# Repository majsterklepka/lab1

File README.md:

# Electronics Workshops
electronics laboratory

Hi! Here is my job, passion and profession. This repository is part of my electronic workbench. Here I will be publish my project used in my everyday jobs. I think it so ourselves, that is cheap as will be buy in the online shops, and I do that.

What will be included into repository:

- power supplies
- dev board
- voltmeters, ammeters, frequency meters, RLC meters etc.
- multiple different usage modules usually used in the laboratory
- etc. ...

## Credits

Author: SQ7EQE op Paweł

Personal blog: [majsterklepka.github.io](https://majsterklepka.github.io/ "My Personal Blog")

Contents of that repository are licensed under terms of:

- GNU GPLv3
- GNU FDL-1.3
- CC-BY-SA, in some reason

**Note:**  
> _Carefully read license, remember the Author, his work is worth something! If you don't want to praise, don't criticize. You can freely modify the projects contained in this repository, remember that!_

**© Paweł Sobótka, 2019 all rights reserved**

At the end ... have fun! Feel free & share these projects with friends!

_MSc Paweł Sobótka (SQ7EQE)_

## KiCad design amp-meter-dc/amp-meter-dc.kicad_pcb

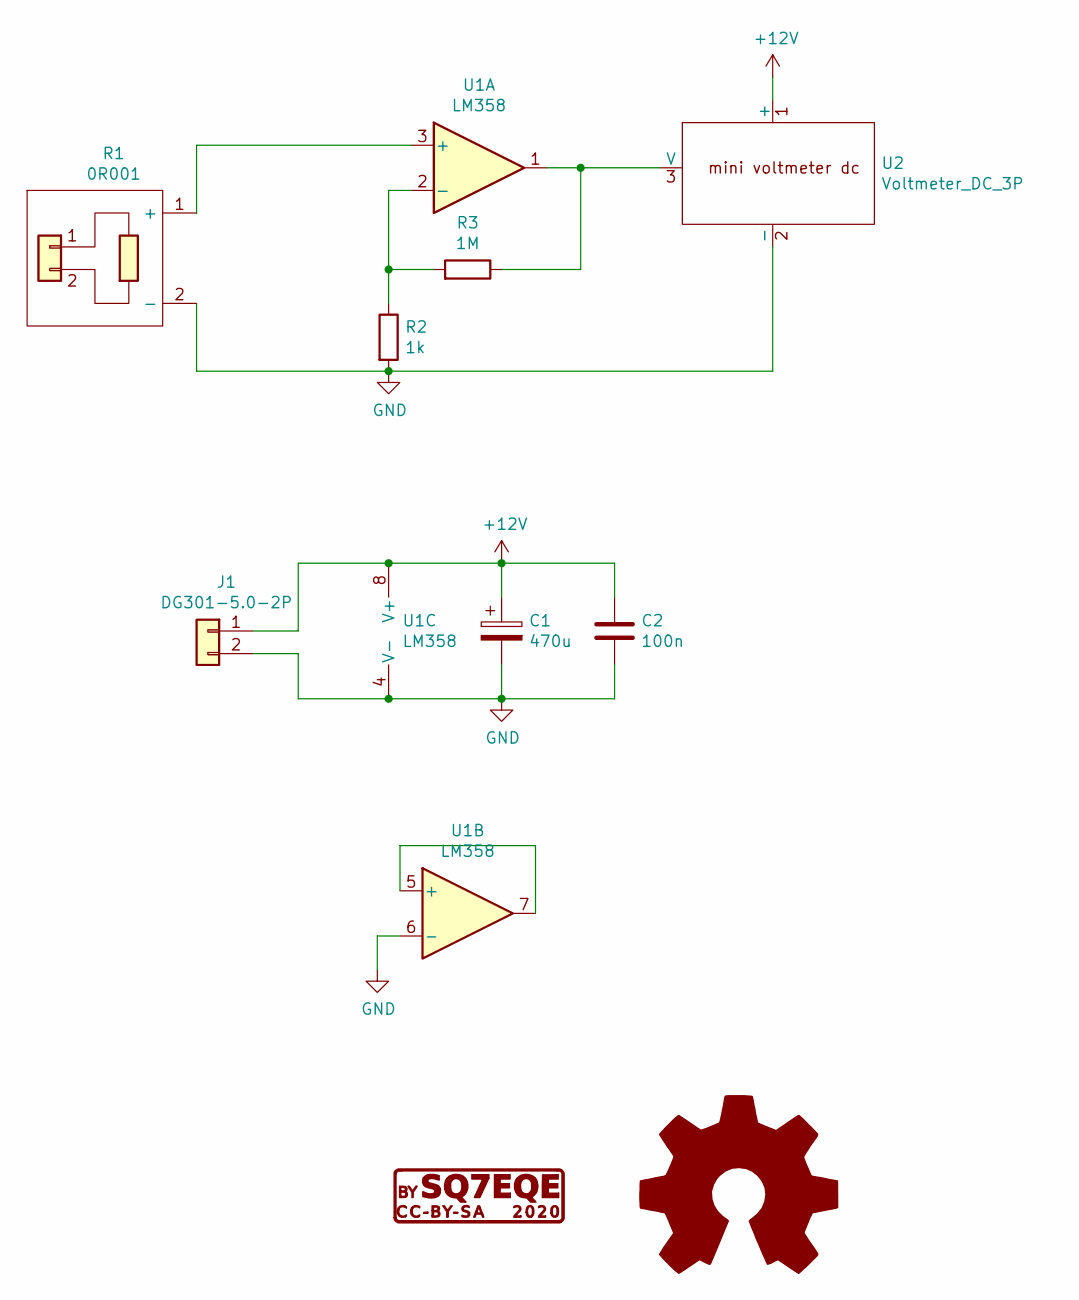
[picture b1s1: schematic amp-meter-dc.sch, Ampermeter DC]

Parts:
C1: 470u; CP_Radial_D8.0mm_P5.00mm
C2: 100n; C_Rect_L7.0mm_W2.0mm_P5.00mm
G1: CC-BY-SA; cc-by-sa
G2: Logo_Open_Hardware_Large; OSHW-Logo2_9.8x8mm_SilkScreen
J1: DG301-5.0-2P
R1: 0R001; bocznik-001
R2: 1k; R_Axial_DIN0204_L3.6mm_D1.6mm_P7.62mm_Horizontal
R3: 1M; R_Axial_DIN0204_L3.6mm_D1.6mm_P7.62mm_Horizontal
U1: LM358; DIP-8_W7.62mm
U2: Voltmeter_DC_3P; mini-voltmeter-dc

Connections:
+12V: C1.1, C2.1, J1.1, U1.8 (V+), U2.1 (+)
GND: C1.2, C2.2, J1.2, R1.2 (-), R2.2, U1.4 (V-), U1.6 (-), U2.2 (-)
unnamed: R1.1 (+), U1.3 (+)
unnamed: R2.1, R3.2, U1.2 (-)
unnamed: R3.1, U1.1, U2.3 (V)
unnamed: U1.5 (+), U1.7

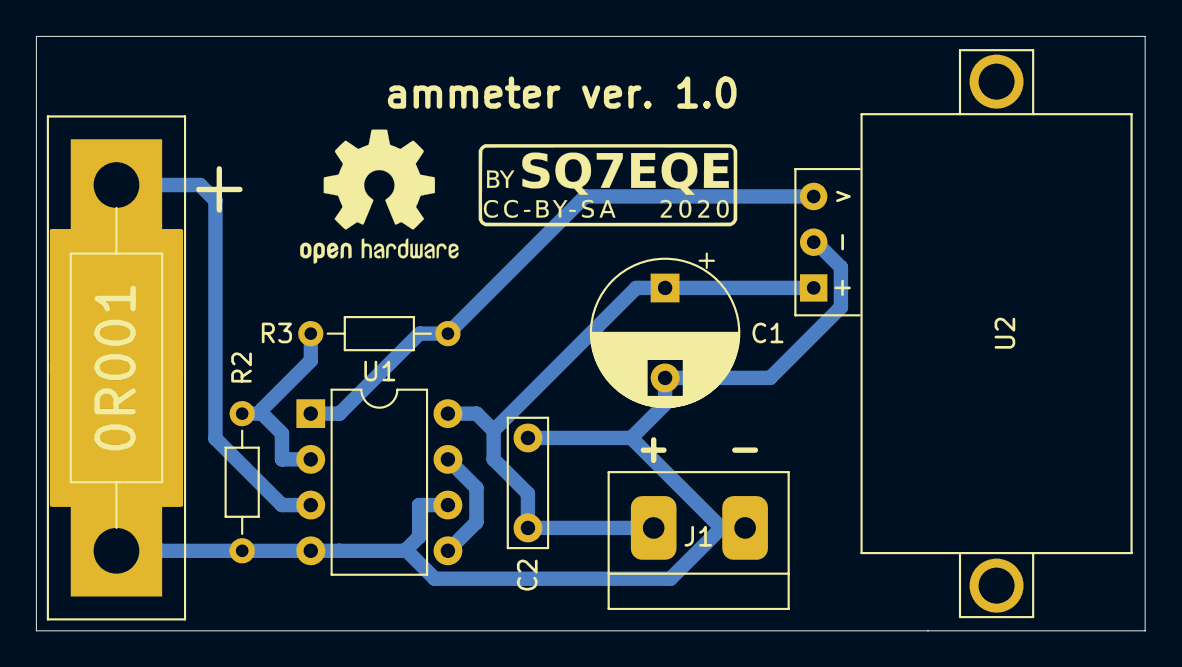
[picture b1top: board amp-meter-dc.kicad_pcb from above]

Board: 2 copper layers, 61.6 x 33.0 mm, 10 parts (0 on the bottom side), 6 nets.

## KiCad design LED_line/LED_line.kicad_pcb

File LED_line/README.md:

# LED strip with eight diodes
electronics workshop

Hi! LED strip for use in any project, inspired by the [avr-gcc](http://hobby.abxyz.bplaced.net/index.php?pid=4&cid=1 "Internetowy kurs avr-gcc") course. Below a PCB 3D view, next as description picture up.

Here we have a schematic sheet:

And what is obviously, project of PCB:

Of course, all project files are included in this folder, with Gerber picture too. Project is very easy to copy, doesn't needs dual side laminate, can be make with thermotransfer method of PCB production in home workshops laboratory.

Have a fun with that project! Be carefully of hot iron!

_MSc. Paweł Sobótka (SQ7EQE)_

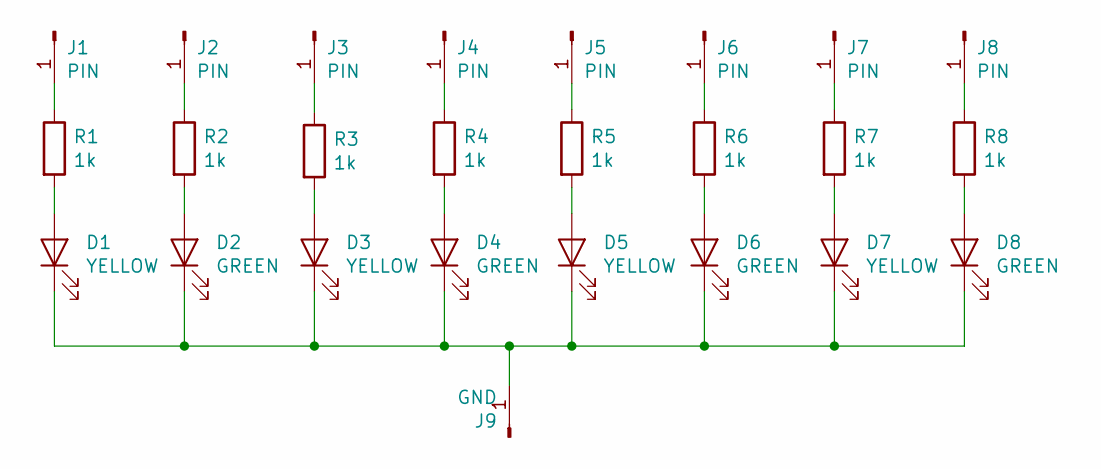
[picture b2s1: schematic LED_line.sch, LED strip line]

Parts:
D1, D3, D5, D7: YELLOW; LED_D3.0mm
D2, D4, D6, D8: GREEN; LED_D3.0mm
J1, J2, J3, J4, J5, J6, J7, J8: PIN; pin_in_01x01
J9: GND; pin_in_01x01
R1, R2, R3, R4, R5, R6, R7, R8: 1k; R_Axial_DIN0204_L3.6mm_D1.6mm_P7.62mm_Horizontal

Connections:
unnamed: D1.1 (K), D2.1 (K), D3.1 (K), D4.1 (K), D5.1 (K), D6.1 (K), D7.1 (K), D8.1 (K), J9.1
unnamed: D1.2 (A), R1.2
unnamed: D2.2 (A), R2.2
unnamed: D3.2 (A), R3.2
unnamed: D4.2 (A), R4.2
unnamed: D5.2 (A), R5.2
unnamed: D6.2 (A), R6.2
unnamed: D7.2 (A), R7.2
unnamed: D8.2 (A), R8.2
unnamed: J1.1, R1.1
unnamed: J2.1, R2.1
unnamed: J3.1, R3.1
unnamed: J4.1, R4.1
unnamed: J5.1, R5.1
unnamed: J6.1, R6.1
unnamed: J7.1, R7.1
unnamed: J8.1, R8.1

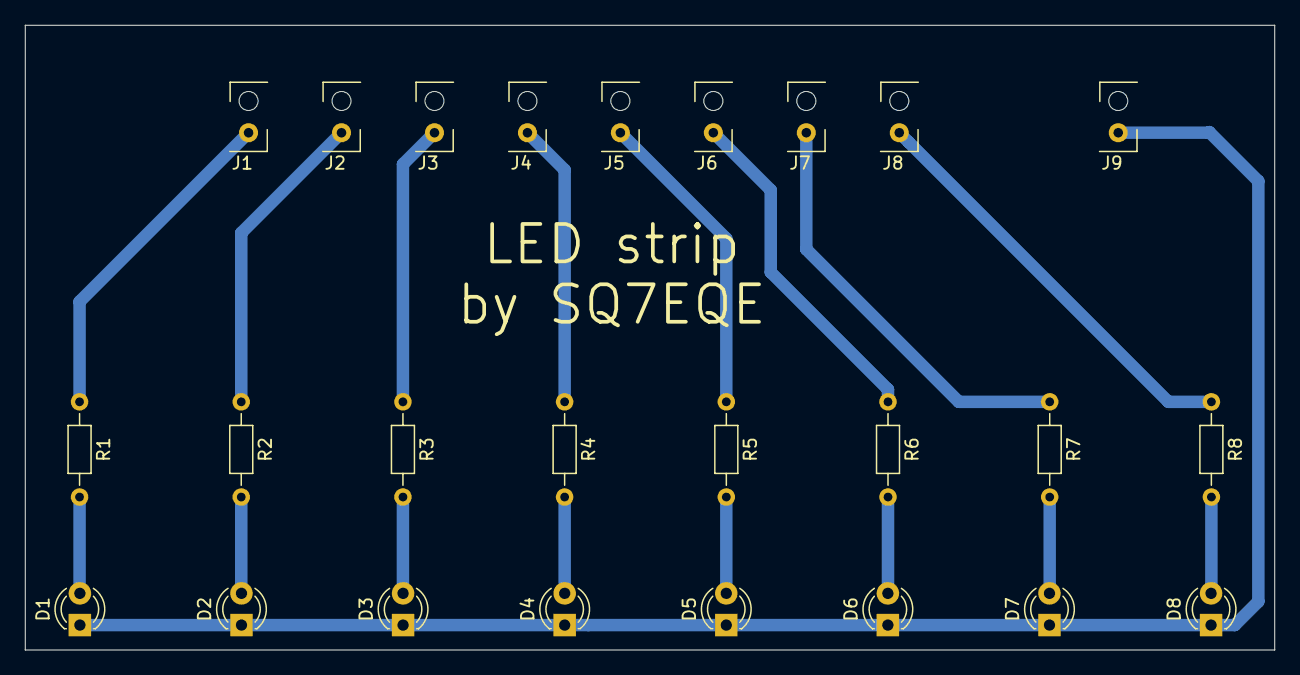
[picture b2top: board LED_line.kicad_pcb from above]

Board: 2 copper layers, 100.0 x 50.0 mm, 25 parts (0 on the bottom side), 17 nets.

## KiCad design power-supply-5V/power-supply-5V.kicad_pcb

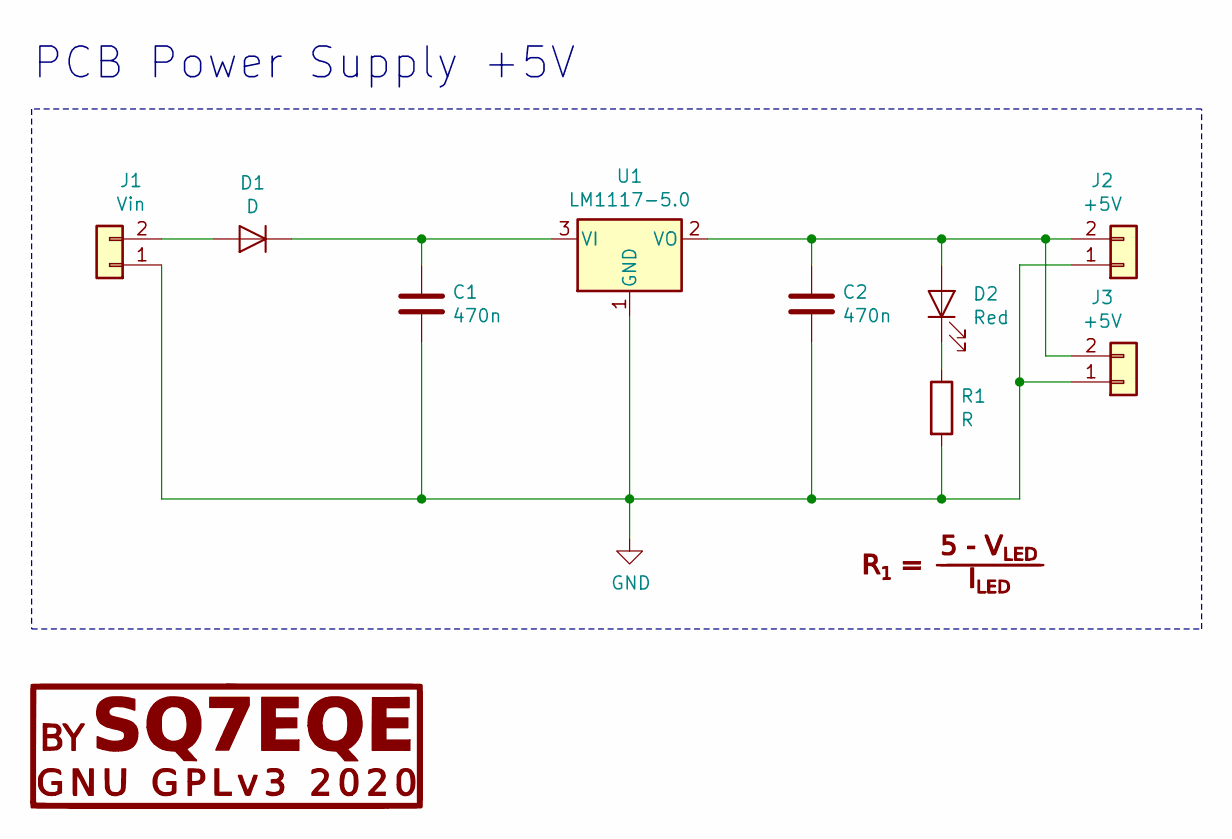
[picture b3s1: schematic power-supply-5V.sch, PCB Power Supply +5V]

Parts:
C1, C2: 470n; C_0805_2012Metric_Pad1.15x1.40mm_HandSolder
D1: D; D_1206_3216Metric_Pad1.42x1.75mm_HandSolder
D2: Red; LED_1206_3216Metric_Pad1.42x1.75mm_HandSolder
J1: Vin; conn_v_in_2x01_508
J2, J3: +5V; conn_v_out_2x03_2.54
R1: R; R_1206_3216Metric_Pad1.42x1.75mm_HandSolder
U1: LM1117-5.0; SOT-223

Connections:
GND: C1.2, C2.2, J1.1, J2.1, J3.1, R1.2, U1.1 (GND)
unnamed: C1.1, D1.1 (K), U1.3 (VI)
unnamed: C2.1, D2.2 (A), J2.2, J3.2, U1.2 (VO)
unnamed: D1.2 (A), J1.2
unnamed: D2.1 (K), R1.1

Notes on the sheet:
PCB Power Supply +5V

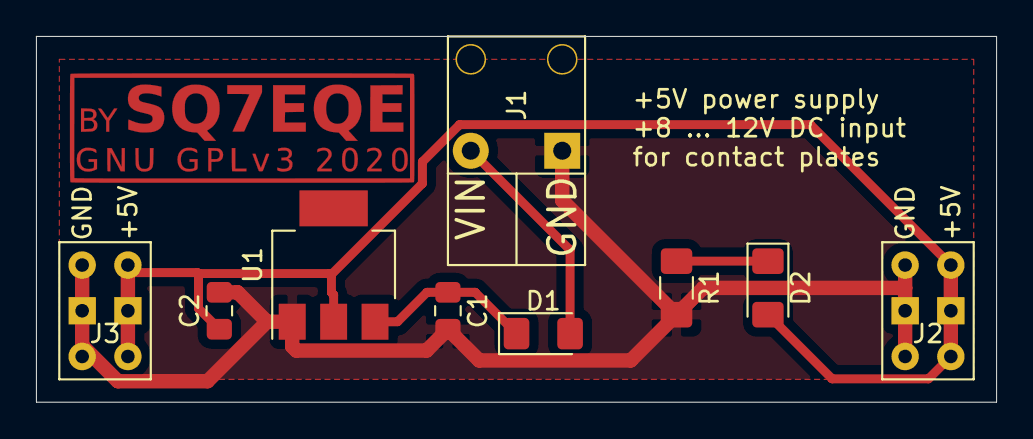
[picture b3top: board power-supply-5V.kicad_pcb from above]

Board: 2 copper layers, 53.3 x 20.3 mm, 9 parts (0 on the bottom side), 5 nets.

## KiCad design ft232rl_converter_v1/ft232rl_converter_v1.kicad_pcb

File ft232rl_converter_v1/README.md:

# USB-TTL-UART-FT232RL Converter
electronics laboratory

Hello, my dear friends!

Today I will tell you about the latest project, USB-TTL-UART-FT232RL converter. It can be said a flagship design, based on the catalog manufacturer's catalog notes. Below, 3D view of the circuit board.

The following elements are needed to build:

- printed circuit board, Gerber files are available in the folder plot /
- FT232RL, the device can be ordered online,
- 100nF x 2 capacitor,
- 10nF x 1 capacitor,
- 10k x 1 resistor,
- 12MHz quartz oscillator,
- ferrite bead x 1,
- MLCC capacitor, 10uF x 1,
- gold pins, straight and angled, 0.1 "pitch
- USB micro B x 1 socket,

The list of all required electronic components is included in the BOM file, available in CSV, ODS and HTML format available in the project's main directory. The schematic diagram of the system is presented below:

And here, an illustrative look at the layout of the circuit board:

It is a system using SMD elements and requires a certain skill in assembly from the contractor due to the size of the elements. All discrete, passive elements are in SMD1206 size and the FT232RL integrated circuit in SSOP-28.

Have fun, feel free and share this project with friends!

Project made available under the terms of the GNU GPLv3 license, project documentation made available under the terms of the FDL-1.3 license.

Thank you and welcome again!

_MSc. Paweł Sobótka (SQ7EQE)_

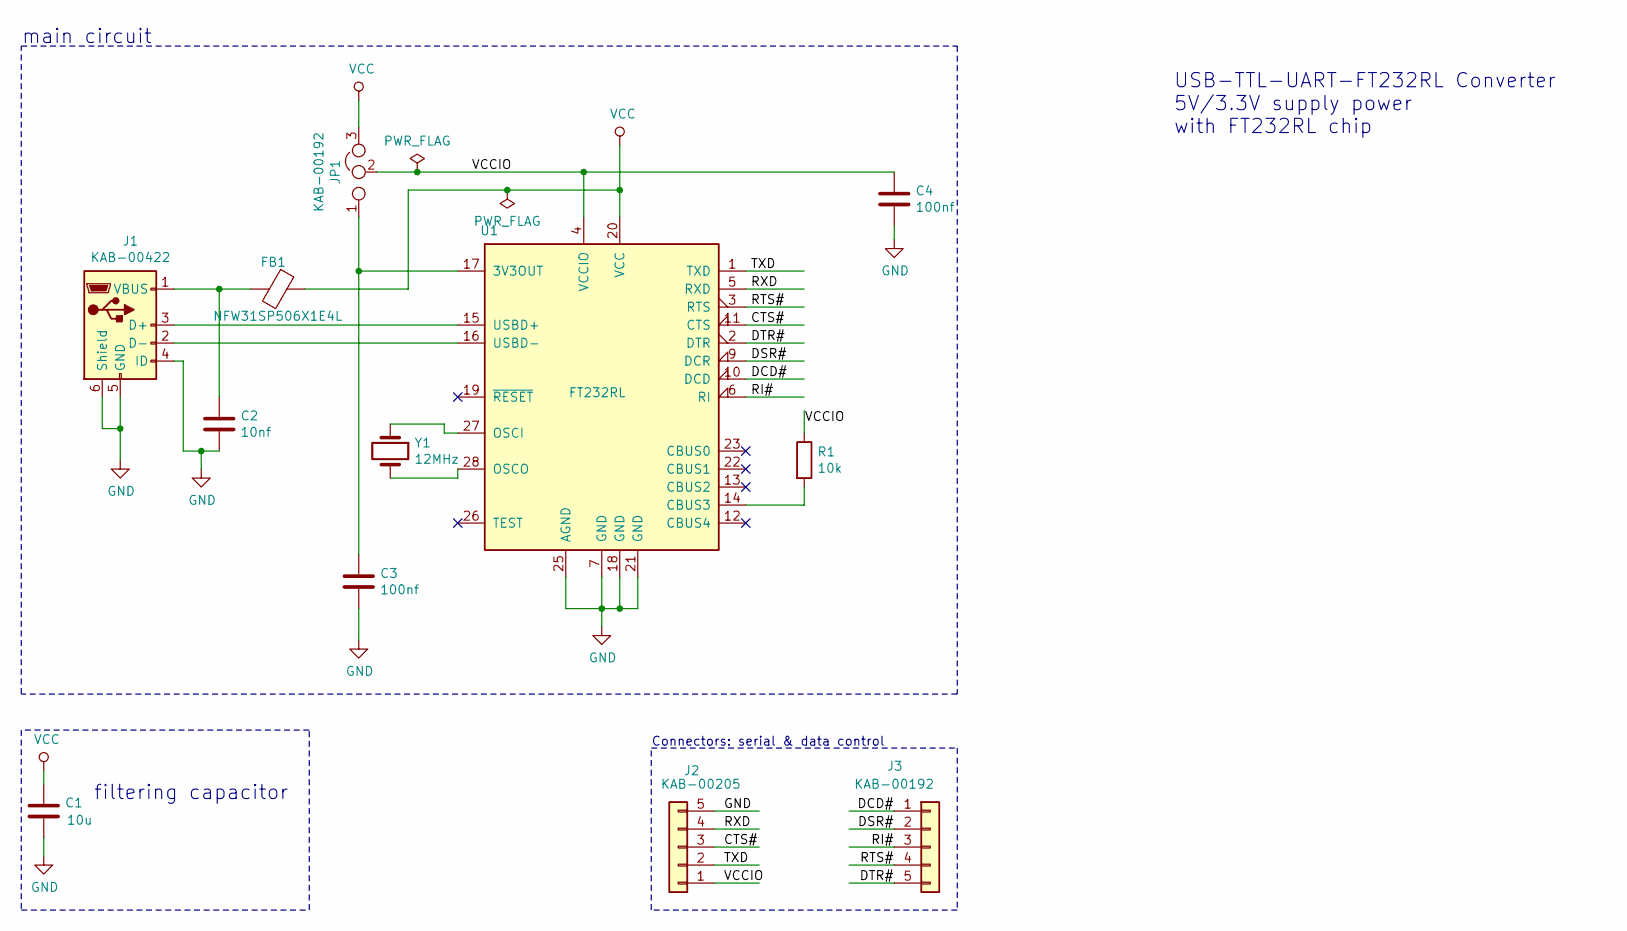
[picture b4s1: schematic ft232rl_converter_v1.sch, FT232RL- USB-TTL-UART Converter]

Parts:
C1: 10u; C_1206_3216Metric_Pad1.42x1.75mm_HandSolder; Part C1206C106K9RACTU
C2: 10nf; C_1206_3216Metric_Pad1.42x1.75mm_HandSolder; Part KC10nF_1206
C3, C4: 100nf; C_1206_3216Metric_Pad1.42x1.75mm_HandSolder; Part KC100nF_1206
FB1: NFW31SP506X1E4L; R_1206_3216Metric_Pad1.42x1.75mm_HandSolder; Part NFW31SP506X1E4L
J1: KAB-00422; USB_Micro-B_Molex_47346-0001; Part KAB-00422
J2: KAB-00205; PinHeader_1x05_P2.54mm_Horizontal; Part KAB-00205
J3: KAB-00192; PinHeader_1x05_P2.54mm_Vertical; Part KAB-00192
JP1: KAB-00192; PinHeader_1x03_P2.54mm_Vertical; Part KAB-00192
R1: 10k; R_1206_3216Metric_Pad1.42x1.75mm_HandSolder; Part R10K_1206
U1: FT232RL; SSOP-28_5.3x10.2mm_P0.65mm; Part FT232RL
Y1: 12MHz; Crystal_HC49-U_Vertical; Part Q12MHZ_N

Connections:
/CTS#: J2.3, U1.11 (CTS)
/DCD#: J3.1, U1.10 (DCD)
/DSR#: J3.2, U1.9 (DCR)
/DTR#: J3.5, U1.2 (DTR)
/RI#: J3.3, U1.6 (RI)
/RTS#: J3.4, U1.3 (RTS)
/RXD: J2.4, U1.5 (RXD)
/TXD: J2.2, U1.1 (TXD)
/VCCIO: C4.1, J2.1, JP1.2, R1.1, U1.4 (VCCIO)
GND: C1.2, C2.2, C3.2, C4.2, J1.4 (ID), J1.5 (GND), J1.6 (Shield), J2.5, U1.7 (GND), U1.18 (GND), U1.21 (GND), U1.25 (AGND)
unnamed: C2.1, FB1.2, J1.1 (VBUS)
unnamed: C3.1, JP1.1, U1.17 (3V3OUT)
unnamed: J1.2 (D-), U1.16 (USBD-)
unnamed: J1.3 (D+), U1.15 (USBD+)
unnamed: R1.2, U1.14 (CBUS3)
unnamed: U1.27 (OSCI), Y1.1
unnamed: U1.28 (OSCO), Y1.2
VCC: C1.1, FB1.1, JP1.3, U1.20 (VCC)

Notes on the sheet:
Connectors: serial & data control
filtering capacitor
USB-TTL-UART-FT232RL Converter 5V/3.3V supply power with FT232RL chip
main circuit

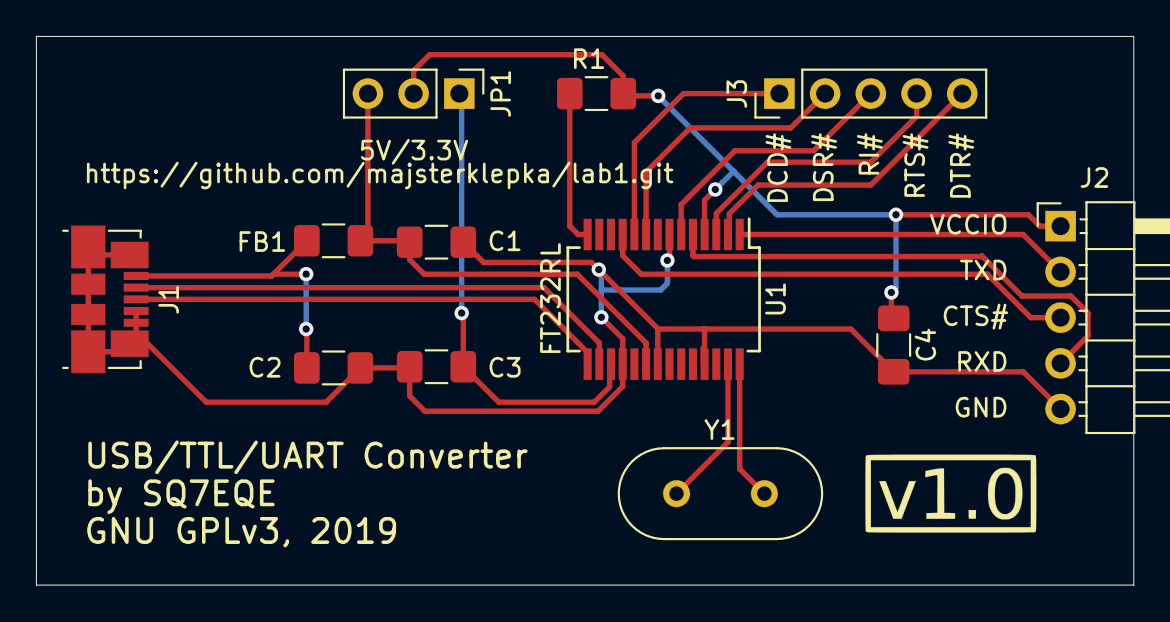
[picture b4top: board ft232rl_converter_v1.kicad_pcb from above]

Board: 2 copper layers, 61.0 x 30.5 mm, 12 parts (0 on the bottom side), 18 nets.

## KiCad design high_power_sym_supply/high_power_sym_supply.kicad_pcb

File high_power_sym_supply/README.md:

# AC/DC symmetric supply
electronics workshop

Hi, My Friends!

Today, I present you with an ac/dc symmetric supply. This project is simply to reproduce, you can use a standard Thermo transfer method, widely described at YouTube. Below you can see a 3D view of PCB layout with components:

Here you can see a schematics sheet, it is very easy, you can reproduce it as you wish:

Of course in that folder, I have included all project files, with Gerber files too.

And here you can see a 2D view of PCB layout:

Have fun & share that project with your friends!

_MSc. Paweł Sobótka (SQ7EQE)_

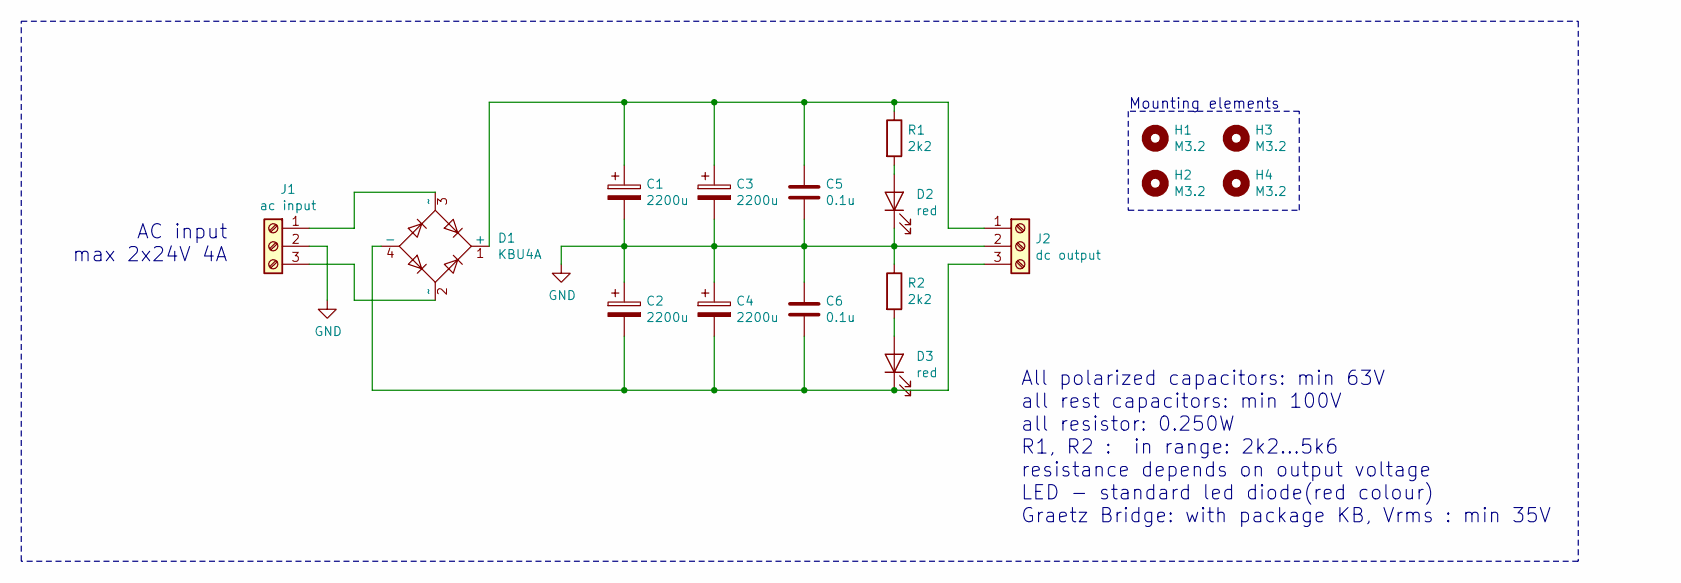
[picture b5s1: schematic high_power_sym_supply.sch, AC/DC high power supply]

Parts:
C1, C2, C3, C4: 2200u; CP_Radial_D18.0mm_P7.50mm
C5, C6: 0.1u; C_Rect_L7.0mm_W2.5mm_P5.00mm
D1: KBU4A; Diode_Bridge_Vishay_KBU
D2, D3: red; LED_D3.0mm
H1, H2, H3, H4: M3.2; MountingHole_3.2mm_M3
J1: ac input; TerminalBlock_Altech_AK300-3_P5.00mm
J2: dc output; TerminalBlock_Altech_AK300-3_P5.00mm
R1, R2: 2k2; R_Axial_DIN0207_L6.3mm_D2.5mm_P10.16mm_Horizontal

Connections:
GND: C1.2, C2.1, C3.2, C4.1, C5.2, C6.1, D2.1 (K), J1.2, J2.2, R2.1
unnamed: C1.1, C3.1, C5.1, D1.1 (+), J2.1, R1.1
unnamed: C2.2, C4.2, C6.2, D1.4 (-), D3.1 (K), J2.3
unnamed: D1.2 (~~), J1.3
unnamed: D1.3 (~~), J1.1
unnamed: D2.2 (A), R1.2
unnamed: D3.2 (A), R2.2

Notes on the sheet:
AC input max 2x24V 4A
Mounting elements
All polarized capacitors: min 63V all rest capacitors: min 100V all resistor: 0.250W R1, R2 : in range: 2k2...5k6 resistance depends on output voltage LED - standard led diode(red colour) Graetz Bridge: with package KB, Vrms : min 35V

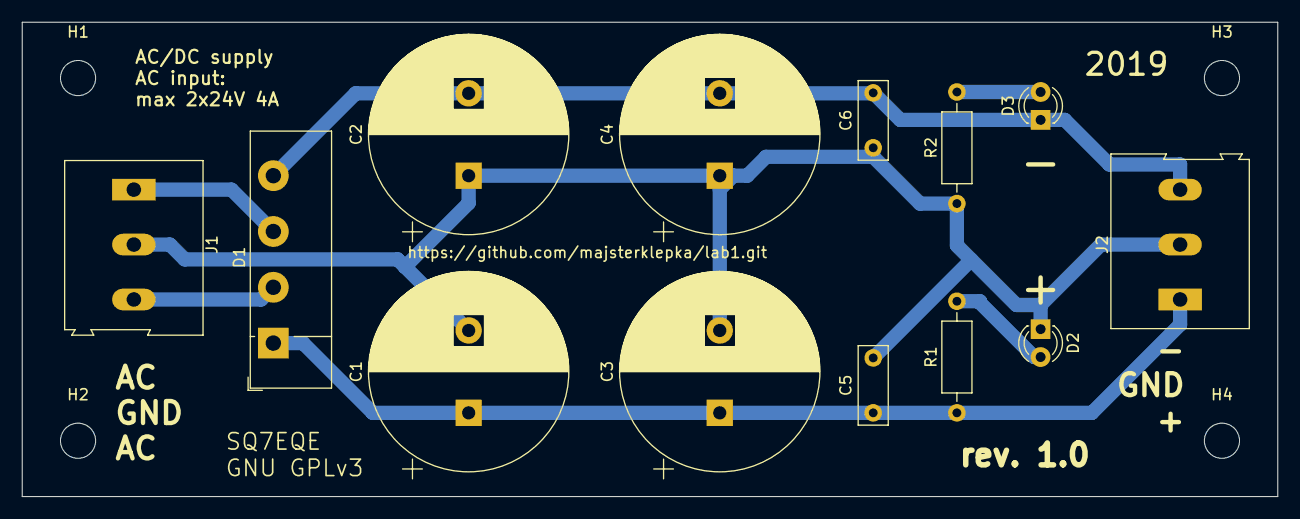
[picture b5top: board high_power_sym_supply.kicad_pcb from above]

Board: 2 copper layers, 114.3 x 43.2 mm, 17 parts (0 on the bottom side), 7 nets.

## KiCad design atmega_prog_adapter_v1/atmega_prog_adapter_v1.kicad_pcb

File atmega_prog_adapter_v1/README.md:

# ATmega adapter
electronics workshop

Hi!

Now here I present a project of ATmega programmer adapter. For what is them? For You! Schematic is very simple, just one ZIF socket, one Kanda socket and a few discrete elements. Project was made with use of KiCad, and graphics are prepare with use of Inkscape. Below I present a Schematic Sheet:

This adapter is used for flashing following devices:

- ATmega48A
- ATmega48PA
- ATmega88A
- ATmega88PA
- ATmega168A
- ATmega168PA
- ATmega328
- ATmega328P

Of course this adapter needs to work a programmer, for example: USBasp or ArduinoISP. Below is shown 3D view of PCB Layout(without showing elements):

and here, is shown a 2d view of PCB Layout:

These all programmers, their projects are published in my repository [here](https://github.com/majsterklepka/avr-programmers.git "MajsterKlepka AVR-PROGRAMMERS Repo")

Have a fun and do not wake up the neighbors during night fun, because this occupation is very addictive and exciting! Feel free and share this project with friends!

_MSc. Paweł Sobótka (SQ7EQE)_

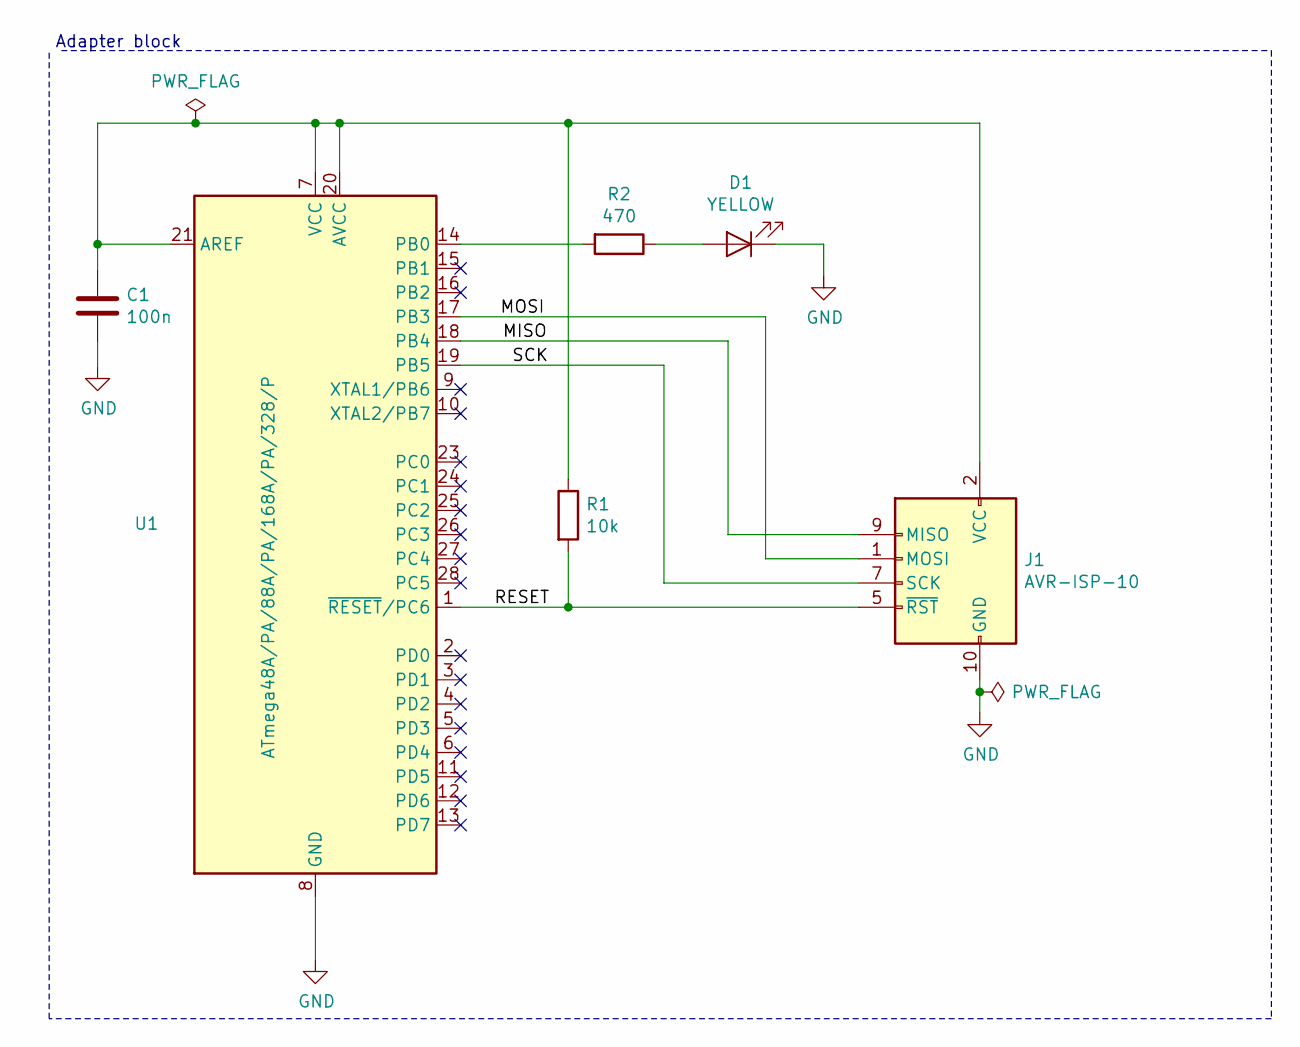
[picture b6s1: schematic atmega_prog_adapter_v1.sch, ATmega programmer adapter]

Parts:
C1: 100n; C_Disc_D5.0mm_W2.5mm_P2.50mm
D1: YELLOW; LED_D3.0mm
J1: AVR-ISP-10; IDC-Header_2x05_P2.54mm_Vertical
R1: 10k; R_Axial_DIN0207_L6.3mm_D2.5mm_P7.62mm_Horizontal
R2: 470; R_Axial_DIN0207_L6.3mm_D2.5mm_P7.62mm_Horizontal
U1: ATmega48A/PA/88A/PA/168A/PA/328/P; DIP_Socket-28_W6.9_W7.62_W10.16_W12.7_W13.5_3M_228-4817-00-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

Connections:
/MISO: J1.9 (MISO), U1.18 (PB4)
/MOSI: J1.1 (MOSI), U1.17 (PB3)
/RESET: J1.5 (~RST), R1.2, U1.1 (~RESET~/PC6)
/SCK: J1.7 (SCK), U1.19 (PB5)
GND: C1.2, D1.1 (K), J1.4 (GND), J1.6 (GND), J1.8 (GND), J1.10 (GND), U1.8 (GND), U1.22 (GND)
unnamed: C1.1, J1.2 (VCC), R1.1, U1.7 (VCC), U1.20 (AVCC), U1.21 (AREF)
unnamed: D1.2 (A), R2.1
unnamed: R2.2, U1.14 (PB0)

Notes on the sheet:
Adapter block

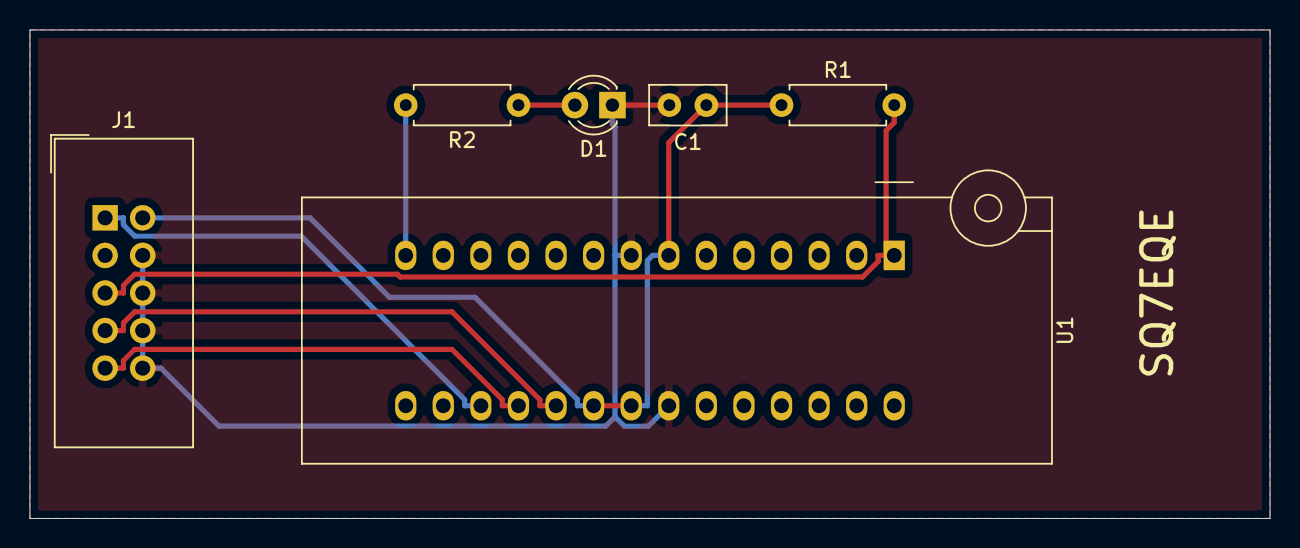
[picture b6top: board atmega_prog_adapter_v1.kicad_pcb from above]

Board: 2 copper layers, 83.8 x 33.0 mm, 6 parts (0 on the bottom side), 8 nets.

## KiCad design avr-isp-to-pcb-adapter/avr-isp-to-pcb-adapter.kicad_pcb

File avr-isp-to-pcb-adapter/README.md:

# AVR ISP to PCB Adapter
electronics workshop

My proposal for today: a small dimension PCB with IDC connector, size 18mm x 23mm rounded. For what it is? If you work with microcontrollers, and contact plates, that project is dedicated for you. This is IDC to contact plates adapter. Below you can see a picture with a 3D view of full design. Project is very simple, size between connectors is equal 3 x 2.54 mm and is fully compatible with most contact plates 

Schematic sheet is present below and of course, as KiCad project into this folder:

And, as you can see, PCB layout project:

Have fun with that project!

_MSc. Paweł Sobótka (SQ7EQE)_

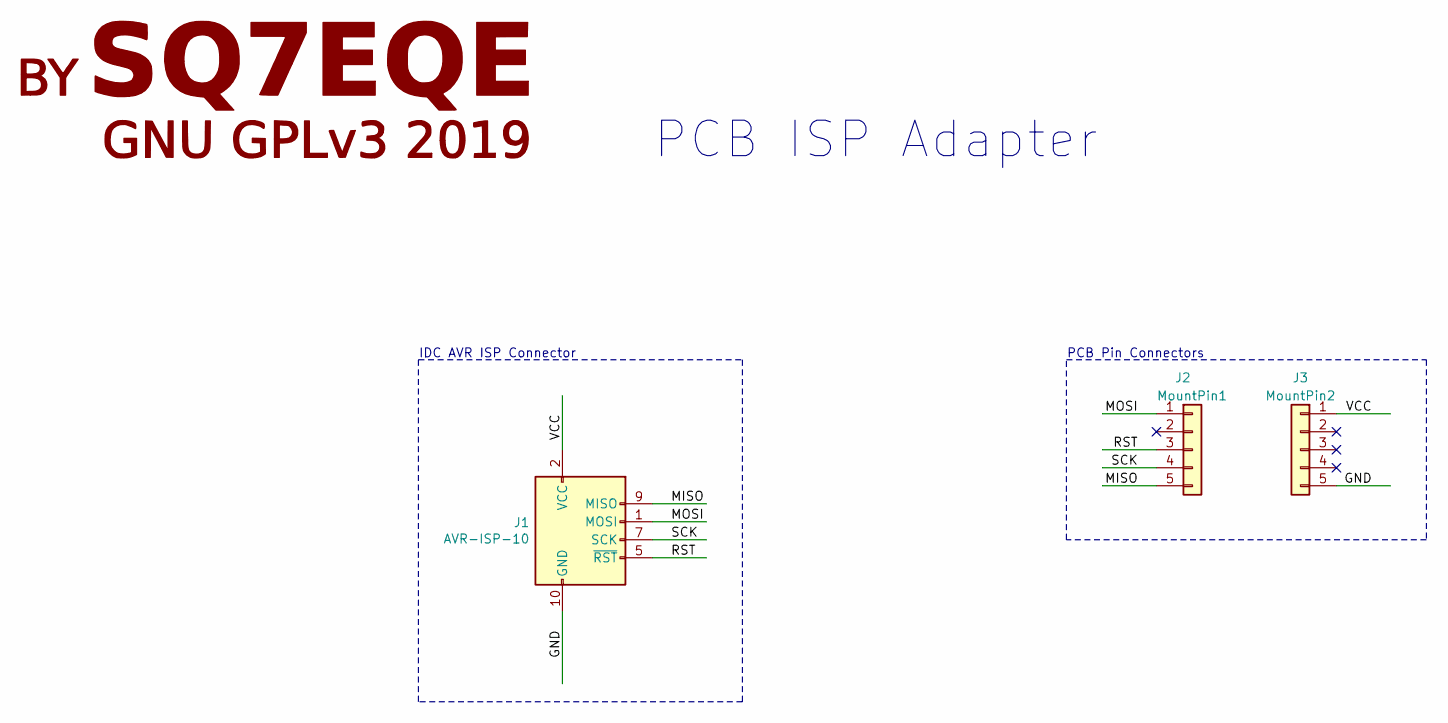
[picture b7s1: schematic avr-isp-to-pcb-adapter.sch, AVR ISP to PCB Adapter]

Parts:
J1: AVR-ISP-10; IDC-Header_2x05_P2.54mm_Vertical
J2: MountPin1; PinHeader_1x05_P2.54mm_Vertical
J3: MountPin2; PinHeader_1x05_P2.54mm_Vertical

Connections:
/GND: J1.4 (GND), J1.6 (GND), J1.8 (GND), J1.10 (GND), J3.5
/MISO: J1.9 (MISO), J2.5
/MOSI: J1.1 (MOSI), J2.1
/RST: J1.5 (~RST), J2.3
/SCK: J1.7 (SCK), J2.4
/VCC: J1.2 (VCC), J3.1

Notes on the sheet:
PCB Pin Connectors
IDC AVR ISP Connector
PCB ISP Adapter

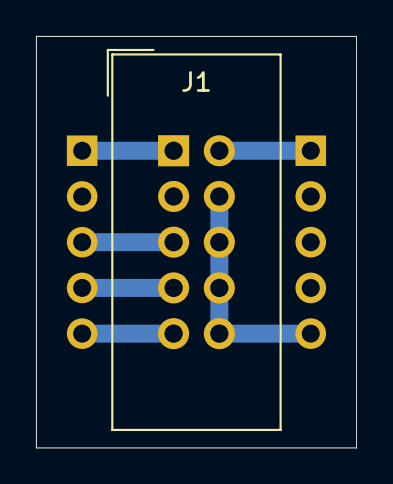
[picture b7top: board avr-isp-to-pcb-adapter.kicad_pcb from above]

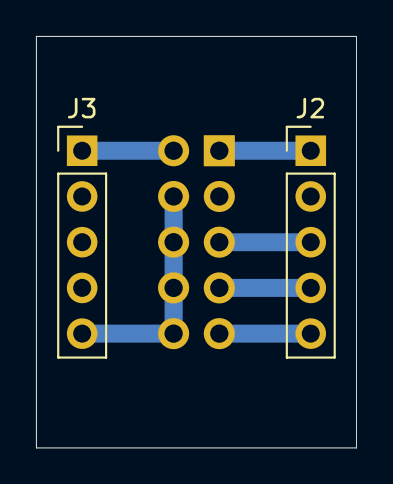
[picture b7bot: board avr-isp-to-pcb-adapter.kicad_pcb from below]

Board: 2 copper layers, 17.8 x 22.9 mm, 3 parts (2 on the bottom side), 6 nets.

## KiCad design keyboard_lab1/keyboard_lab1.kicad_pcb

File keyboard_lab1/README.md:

# Dev Board KeyPad Lab1
electronics workshop

Hi! There we have a Project of KeyPad. All jobs was made with KiCad and Inkscape. Schematic Sheet is shown below:

Of course, all project file are included into this folder. I prepare PCB Layout project too:

Here we have a 3D view of PCB layout yet:

Especially for you, I prepare a 2D image with black&white view of PCB, for build yours own board with thermotransfer method here is an image(in PNG image format 300dpi resolution): [pict. 4](https://github.com/majsterklepka/lab1/raw/master/keyboard_lab1/drawings/keyboard_lab1-prep-brd.png "PCB Layout Image")

_MSc. Paweł Sobótka (SQ7EQE)_

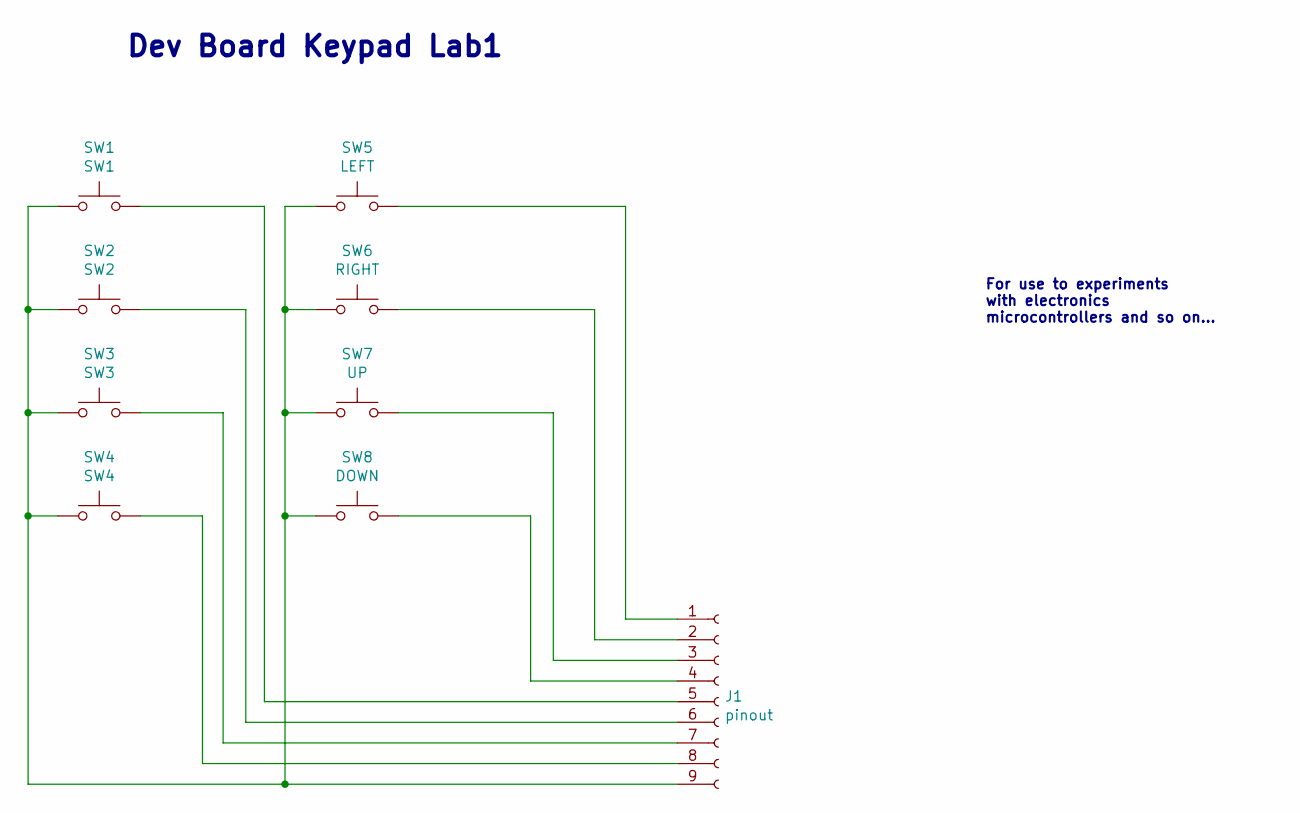
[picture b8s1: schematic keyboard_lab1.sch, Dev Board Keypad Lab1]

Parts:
J1: pinout; con_pingold_9_P2.54
SW1: SW1; SW_PUSH_6mm_H4.3mm
SW2: SW2; SW_PUSH_6mm_H4.3mm
SW3: SW3; SW_PUSH_6mm_H4.3mm
SW4: SW4; SW_PUSH_6mm_H4.3mm
SW5: LEFT; SW_PUSH_6mm_H4.3mm
SW6: RIGHT; SW_PUSH_6mm_H4.3mm
SW7: UP; SW_PUSH_6mm_H4.3mm
SW8: DOWN; SW_PUSH_6mm_H4.3mm

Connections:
unnamed: J1.1, SW5.2
unnamed: J1.2, SW6.2
unnamed: J1.3, SW7.2
unnamed: J1.4, SW8.2
unnamed: J1.5, SW1.2
unnamed: J1.6, SW2.2
unnamed: J1.7, SW3.2
unnamed: J1.8, SW4.2
unnamed: J1.9, SW1.1, SW2.1, SW3.1, SW4.1, SW5.1, SW6.1, SW7.1, SW8.1

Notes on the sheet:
Dev Board Keypad Lab1
For use to experiments with electronics microcontrollers and so on...

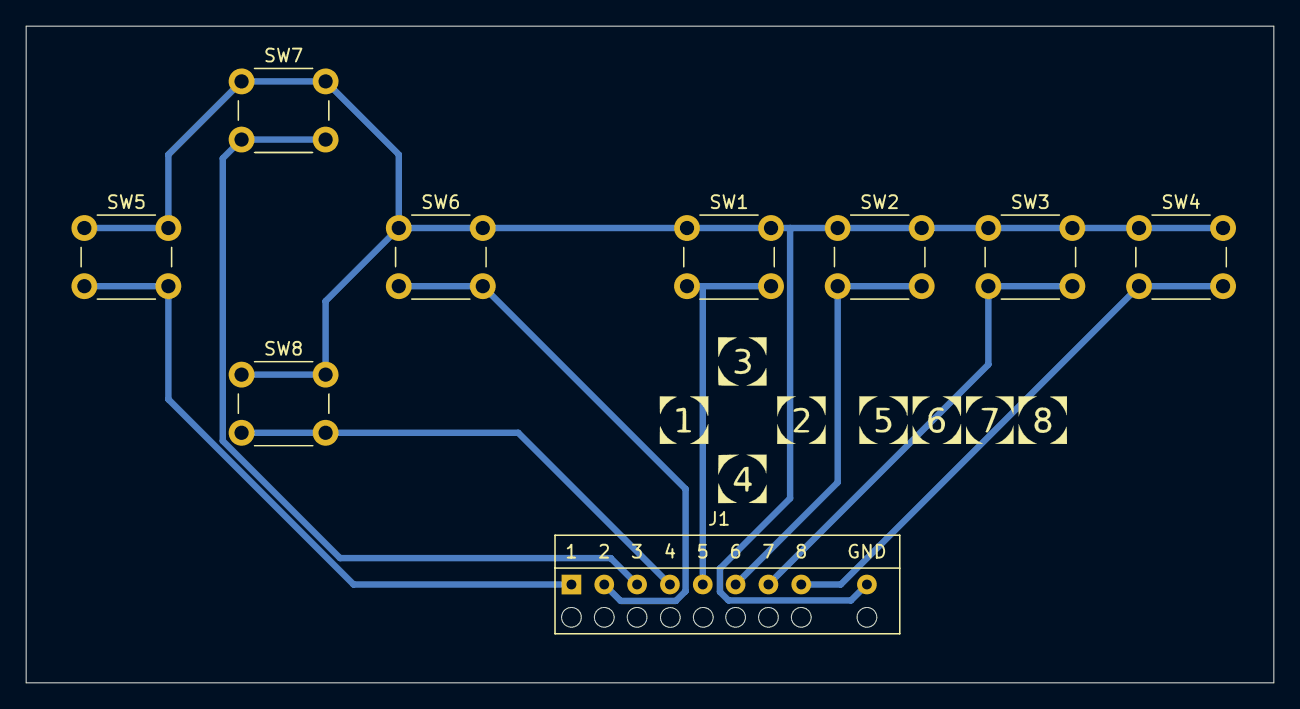
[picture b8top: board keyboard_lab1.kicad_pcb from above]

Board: 2 copper layers, 96.5 x 50.8 mm, 9 parts (0 on the bottom side), 9 nets.

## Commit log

2019-09-18 update: first project
2019-09-18 update: new project
2019-09-18 update: fixed broken file name
2019-09-19 update: fixed filename and paths
2019-09-19 update: fixed grammar issues
2019-09-21 update: include footprint library into projects were it was needed
2019-09-22 new project
2019-09-22 fixed broken file name
2019-09-22 update: add new usability
2019-09-22 update: update image
2019-09-24 update: fixed broken file path
2019-09-25 update: fixed invalid margins around crystal
2019-09-26 update: add website to google index
2019-09-26 update: remove unused file
2019-09-27 update: new projekt
2019-09-30 update: make spelling corrections
2019-10-05 update: new project ready to get
2019-10-06 update: add pcb mounting elements to the project
2019-10-06 update: I fixed bugs with the pcb board layout
2019-10-06 update: I added a more detailed description to the schematic diagram
2019-10-13 update: I have fixed mistake in PCB layout, incorrect distribution of some components
2019-10-13 update: I have fixed bugs with paths, I think so myselfwq
2019-10-13 update: I have fixed bugs with paths, I think so myself
2019-10-13 update: prepare Gerber files for productions
2019-10-13 update: I have prepared files for make own pcb
    all Gerber files works fine with jlcpcb.com and others services
2019-10-20 update: I have included fdl license file into repository
    All documentation are publish and share under terms of these license
2019-10-20 update: I have correct of spelling title before my name
2019-10-20 update: I share a New Project!
    Now about FT232RL and USB-TTL-UART convertions.
2019-10-20 update: a some misspelling corections
2019-11-04 update: update pcb project
2019-11-09 update:new project
2019-11-11 update: update copyright holder
2019-11-17 update: correct a title name of author
2019-11-19 update: new project is ready to get
2019-11-19 update: update PCB design
2019-11-20 update: I have modified a PCB design ...
2019-11-20 update: I have fixed bad path to image
2019-11-21 update: I have re-generate PCB Gerber files
2019-11-21 update: I have re-generate PCB 3D View picture file
2019-11-22 update: new project is ready
2019-11-22 update: update README.md
2019-11-23 update: new project is ready! Have fun!
2019-11-24 update: I have update content of file
2019-11-24 update: remove bad meta content
2020-01-22 update: new projekt is up
2020-01-22 update: fixed path errors
2020-01-31 update: update footprints & Gerber files
2020-02-01 update: new project, power supply
2020-02-01 update: new project, power supply, modification
2020-02-01 update: add new files & update README.md
2020-05-25 updated the file
2020-09-27 new project
    a classical mb-102 breadboard power supply
    with 5.0V and 3.3V output
    based at Internet Reasearch jobs
2020-09-27 new project
    base board for AVR experiments with ATtiny2313a microcontrolers
    included power supply and avr-isp-10 connector
2020-09-27 new project
    amper meter, project based at contest question published in EdW
    my version has a pcb based current shunt and uses typical 0.28''
    3-wired mini voltmeter
2020-09-27 new kicad footprint library files
    I completed kicad footprints used in my projects
    perhaps I will separate them into separate repo(in future)

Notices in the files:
amp-meter-dc/amp-meter-dc.sch:
CC-BY-SA 4.0
ft232rl_converter_v1/ft232rl_converter_v1.kicad_pcb:
GNU GPLv3, 2019
